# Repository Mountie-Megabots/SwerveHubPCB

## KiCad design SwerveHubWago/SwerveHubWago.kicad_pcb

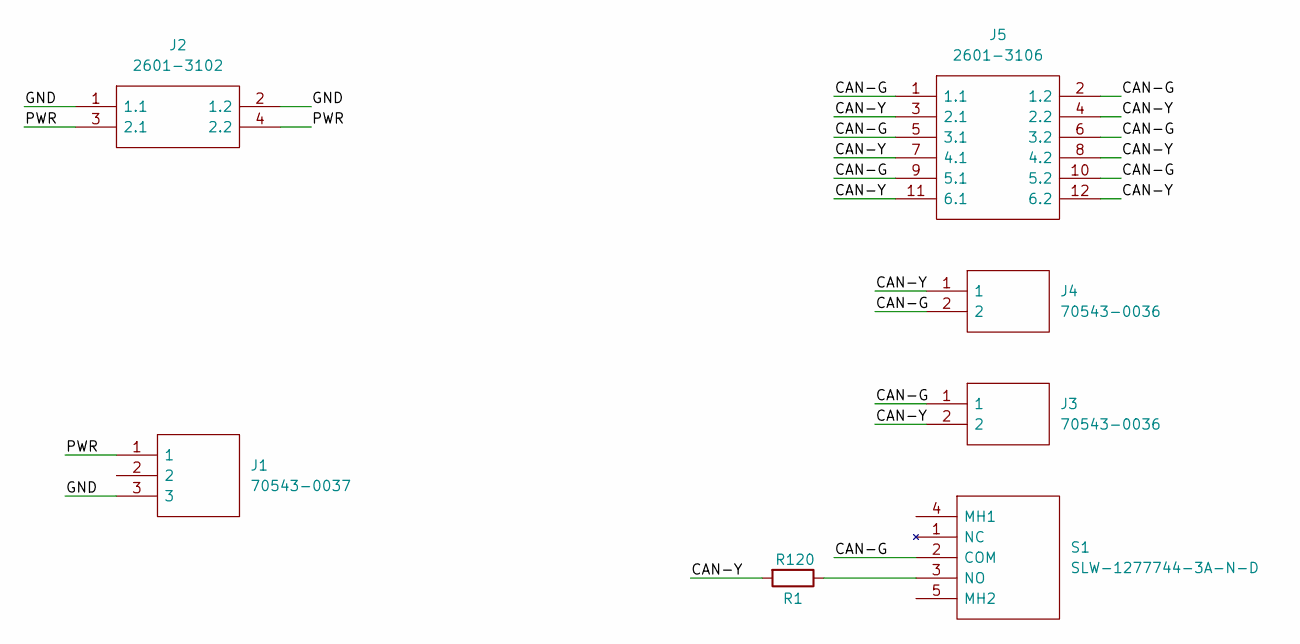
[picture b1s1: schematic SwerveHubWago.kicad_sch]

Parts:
J1: 70543-0037; SHDR3W97P0X254_1X3_1017X660X1181P; Manufacturer_Part_Number 70543-0037; Mouser Part Number 538-70543-0037
J2: 2601-3102; 26013102; Manufacturer_Part_Number 2601-3102
J3, J4: 70543-0036; SHDR2W64P0X254_1X2_737X660X1194P; Manufacturer_Part_Number 70543-0036; Mouser Part Number 538-70543-0036
J5: 2601-3106; 26013106; Manufacturer_Part_Number 2601-3106
R1: R120; R_0805_2012Metric_Pad1.20x1.40mm_HandSolder
S1: SLW-1277744-3A-N-D; SLW12777443AND; Manufacturer_Part_Number SLW-1277744-3A-N-D; Mouser Part Number 179-SLW12777443AND

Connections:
/CAN-G: J3.1, J4.2, J5.1 (1.1), J5.2 (1.2), J5.5 (3.1), J5.6 (3.2), J5.9 (5.1), J5.10 (5.2), S1.2 (COM)
/CAN-Y: J3.2, J4.1, J5.3 (2.1), J5.4 (2.2), J5.7 (4.1), J5.8 (4.2), J5.11 (6.1), J5.12 (6.2), R1.2
/GND: J1.3, J2.1 (1.1), J2.2 (1.2)
/PWR: J1.1, J2.3 (2.1), J2.4 (2.2)
unnamed: R1.1, S1.3 (NO)

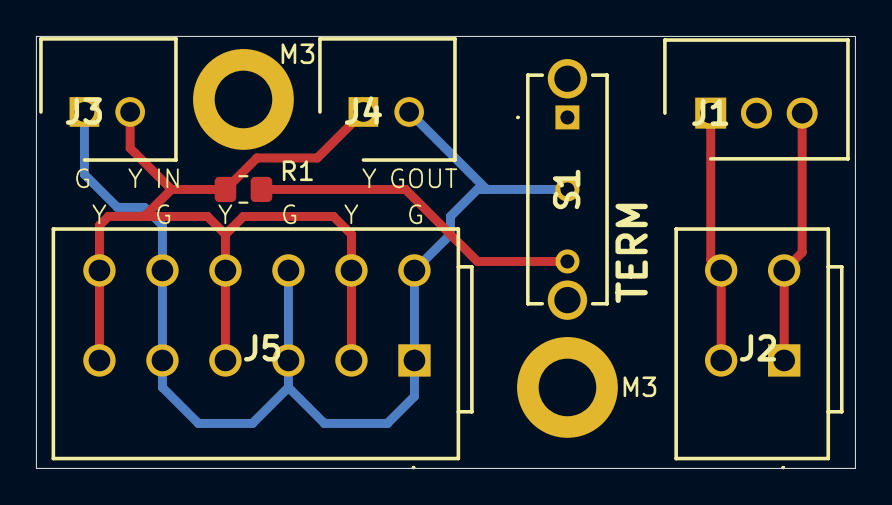
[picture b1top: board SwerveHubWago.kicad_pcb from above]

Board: 2 copper layers, 45.5 x 24.0 mm, 9 parts (0 on the bottom side), 5 nets.

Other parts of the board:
M3, M3#2: MountingHole_3.2mm_M3_DIN965_Pad

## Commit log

2024-12-13 Initial commit
    Board design that uses 10 position Wago 2601 terminal block for CAN and 4 position terminal block for Cancoder power.
2024-12-13 Rev 2
    Switched connecters to two (in/out) Molex SL connectors for CAN and one three pin Molex SL connector for power. Changed Wago terminal blocks to 6 position for CAN and 2 position for power.
2025-01-28 Fixed switch connections
